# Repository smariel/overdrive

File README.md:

# overdrive
Overdrive/Distorsion Pedal

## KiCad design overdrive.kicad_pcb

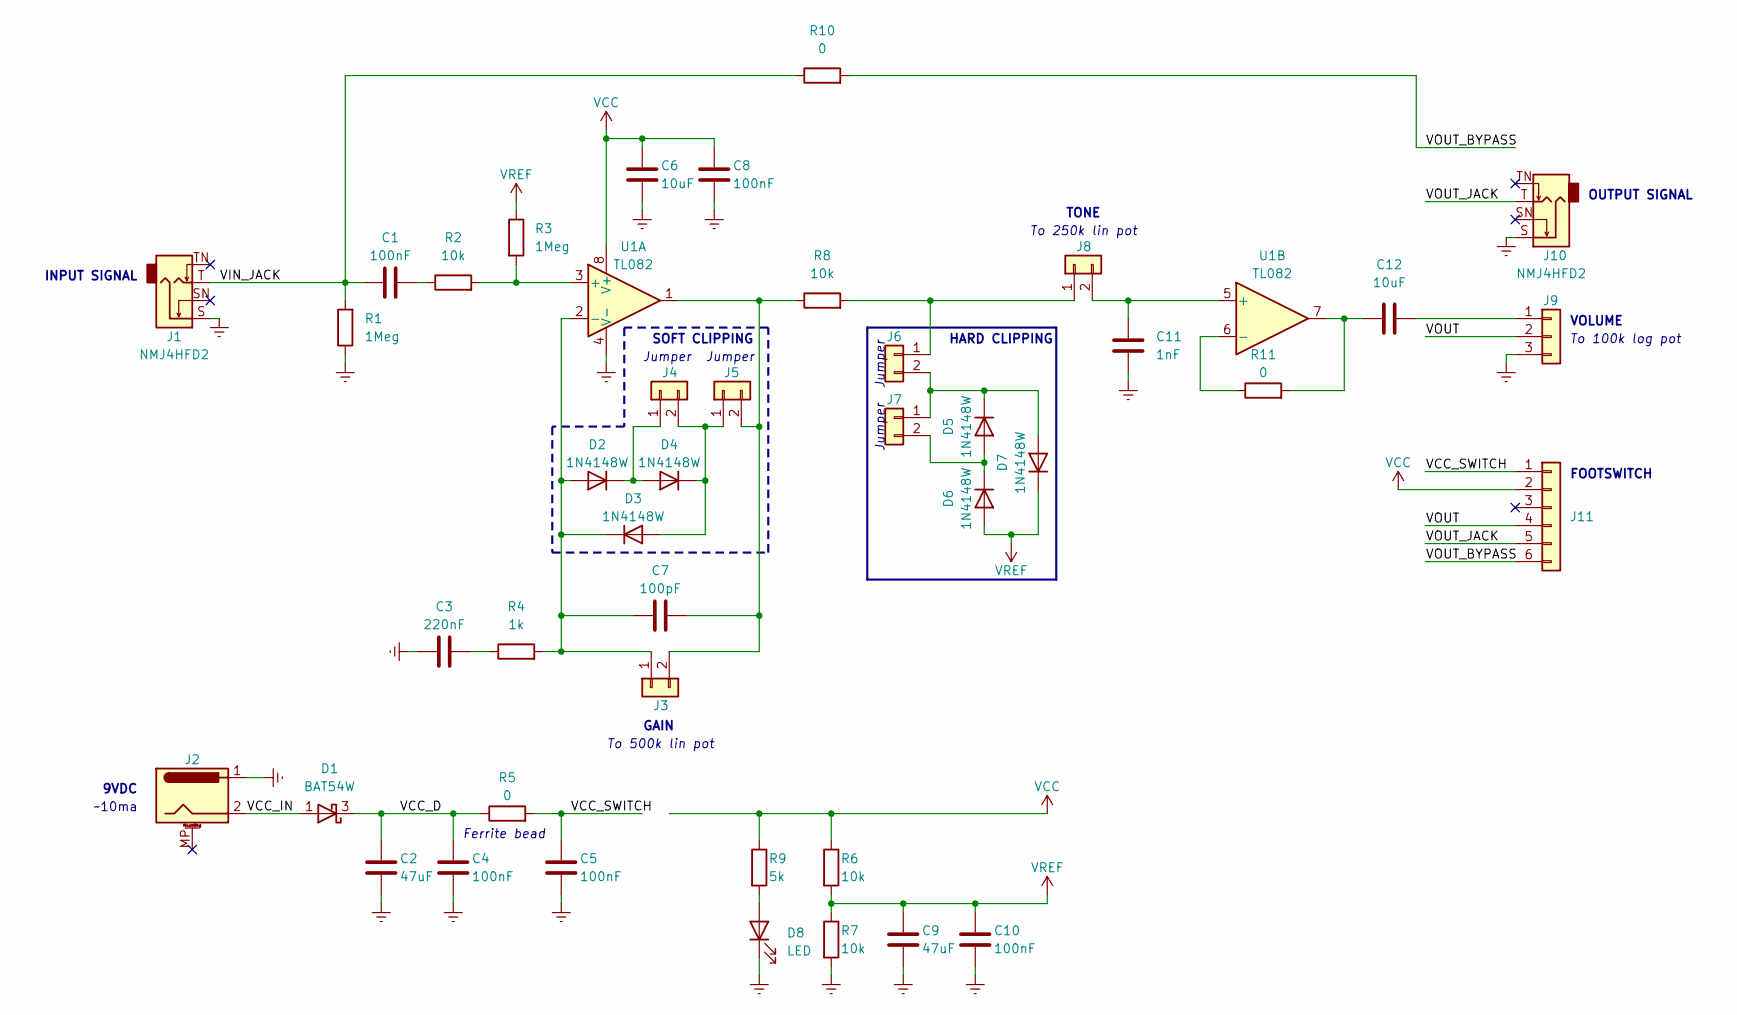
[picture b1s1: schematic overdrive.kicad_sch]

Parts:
C1, C4, C5, C8, C10: 100nF; C_0402_1005Metric_Pad0.74x0.62mm_HandSolder
C2, C9: 47uF; C_1210_3225Metric_Pad1.33x2.70mm_HandSolder
C3: 220nF; C_0402_1005Metric_Pad0.74x0.62mm_HandSolder
C6, C12: 10uF; C_0805_2012Metric_Pad1.18x1.45mm_HandSolder
C7: 100pF; C_0402_1005Metric_Pad0.74x0.62mm_HandSolder
C11: 1nF; C_0402_1005Metric_Pad0.74x0.62mm_HandSolder
D1: BAT54W; SOT-323_SC-70
D2, D3, D4, D5, D6, D7: 1N4148W; D_SOD-123
D8: LED; LED_D5.0mm
J1, J10: NMJ4HFD2; Jack_6.35mm_Neutrik_NMJ4HFD2_Horizontal
J2: Barrel_Jack_MountingPin; BarrelJack_GCT_DCJ200-10-A_Horizontal
J3, J4, J5, J6, J7, J8: Conn_01x02; PinHeader_1x02_P2.54mm_Vertical
J9: Conn_01x03; PinHeader_1x03_P2.54mm_Vertical
J11: Conn_01x06; PinHeader_1x06_P2.54mm_Vertical
R1, R3: 1Meg; R_0402_1005Metric_Pad0.72x0.64mm_HandSolder
R2, R6, R7, R8: 10k; R_0402_1005Metric_Pad0.72x0.64mm_HandSolder
R4: 1k; R_0402_1005Metric_Pad0.72x0.64mm_HandSolder
R5: 0; R_0805_2012Metric_Pad1.20x1.40mm_HandSolder
R9: 5k; R_0402_1005Metric_Pad0.72x0.64mm_HandSolder
R10, R11: 0; R_0402_1005Metric_Pad0.72x0.64mm_HandSolder
U1: TL082; SOIC-8_3.9x4.9mm_P1.27mm

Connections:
/VCC_D: C2.1, C4.1, D1.3 (K), R5.1
/VCC_IN: D1.1 (A), J2.2
/VCC_SWITCH: C5.1, J11.1, R5.2
/VIN_JACK: C1.1, J1.T, R1.2, R10.1
/VOUT: J9.2, J11.4
/VOUT_BYPASS: J11.6, R10.2
/VOUT_JACK: J10.T, J11.5
GNDREF: C2.2, C3.1, C4.2, C5.2, C6.2, C8.2, C9.2, C10.2, C11.2, D8.1 (K), J1.S, J2.1, J9.3, J10.S, R1.1, R7.2, U1.4 (V-)
unnamed: C1.2, R2.1
unnamed: C3.2, R4.1
unnamed: C7.1, D2.2 (A), D3.1 (K), J3.1, R4.2, U1.2 (-)
unnamed: C7.2, J3.2, J5.2, R8.1, U1.1
unnamed: C11.1, J8.2, U1.5 (+)
unnamed: C12.1, R11.2, U1.7
unnamed: C12.2, J9.1
unnamed: D2.1 (K), D4.2 (A), J4.1
unnamed: D3.2 (A), D4.1 (K), J4.2, J5.1
unnamed: D5.1 (K), D7.2 (A), J6.2, J7.1
unnamed: D5.2 (A), D6.1 (K), J7.2
unnamed: D8.2 (A), R9.2
unnamed: J6.1, J8.1, R8.2
unnamed: R2.2, R3.2, U1.3 (+)
unnamed: R11.1, U1.6 (-)
VCC: C6.1, C8.1, J11.2, R6.1, R9.1, U1.8 (V+)
VREF: C9.1, C10.1, D6.2 (A), D7.1 (K), R3.1, R6.2, R7.1

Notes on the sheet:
FOOTSWITCH
INPUT SIGNAL
9VDC
GAIN
OUTPUT SIGNAL
To 100k log pot
~10ma
TONE
VOLUME
To 500k lin pot
Jumper
To 250k lin pot
HARD CLIPPING
SOFT CLIPPING
Ferrite bead

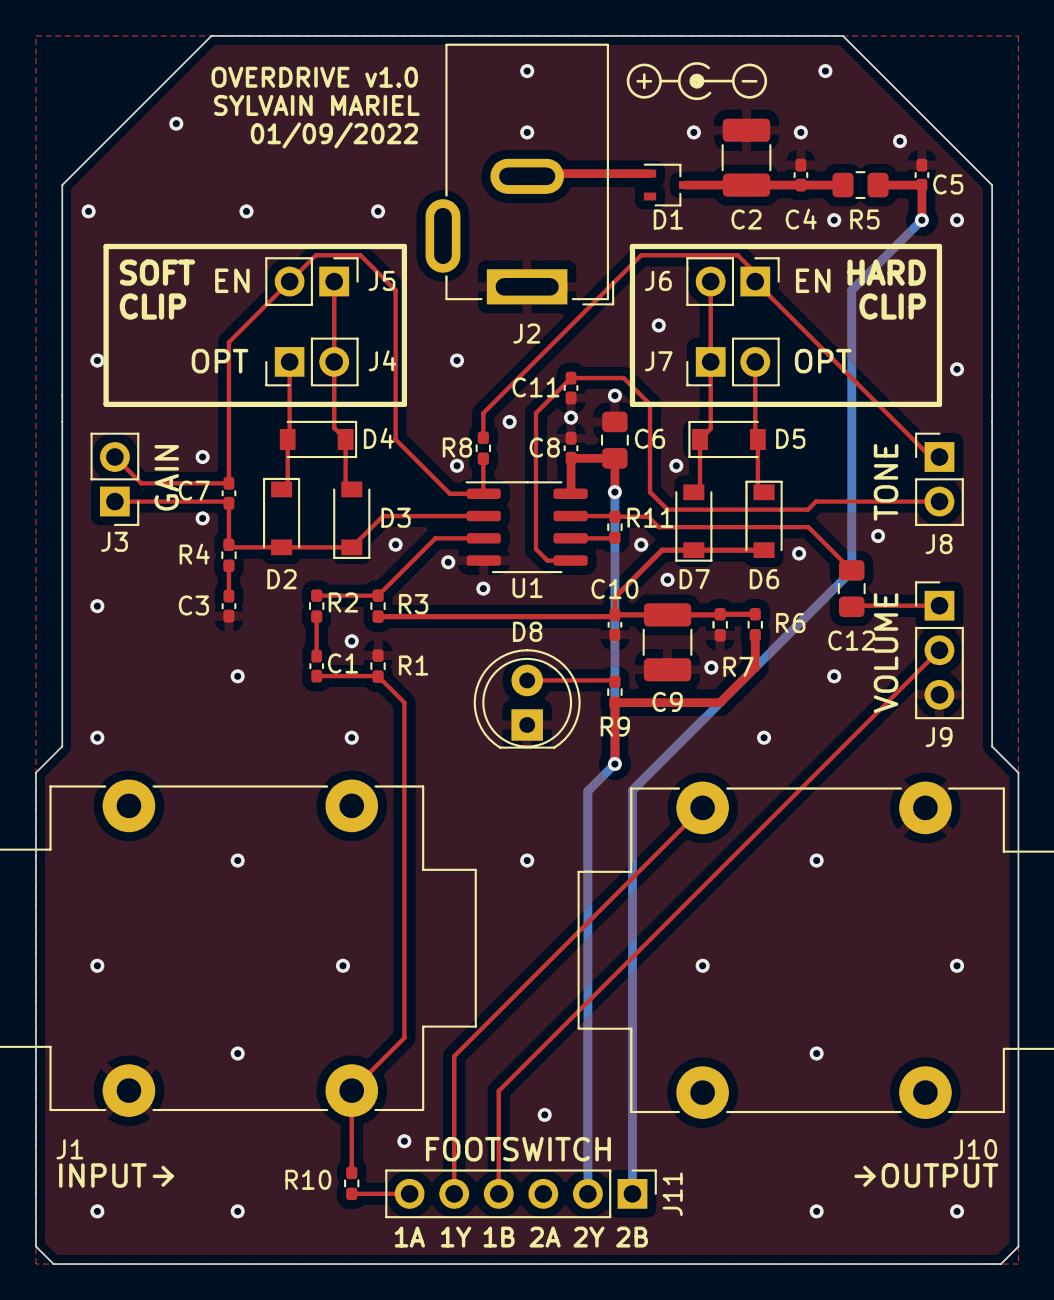
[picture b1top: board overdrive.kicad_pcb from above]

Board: 2 copper layers, 56.0 x 70.0 mm, 43 parts (0 on the bottom side), 25 nets.

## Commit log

2023-01-07 v1.0
2023-01-07 img update
